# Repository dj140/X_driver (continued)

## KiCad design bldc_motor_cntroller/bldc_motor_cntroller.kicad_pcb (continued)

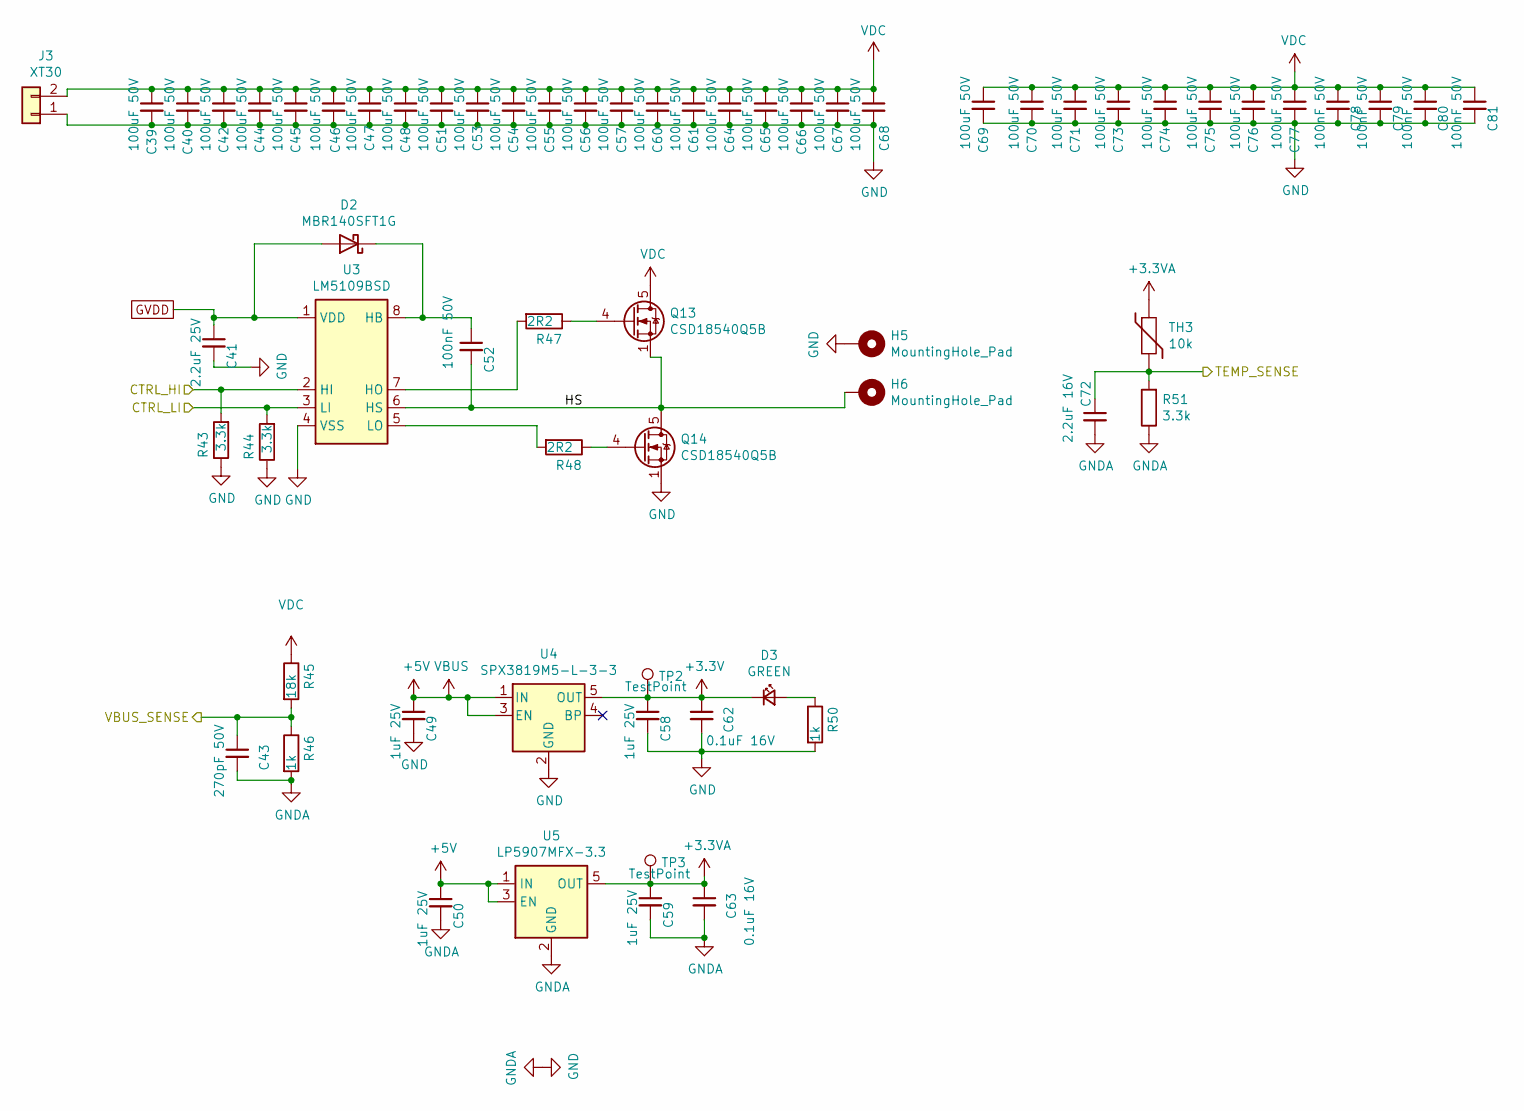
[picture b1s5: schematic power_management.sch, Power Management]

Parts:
C39, C40, C42, C44, C45, C46, C47, C48, C51, C53, C54, C55, C56, C57, C60, C61, C64, C65, C66, C67, C68, C69, C70, C71, C73, C74, C75, C76, C77: 100uF 50V; C_1206_3216Metric; MPN GMK105CC6105MV-F
C41: 2.2uF 25V; C_0402_1005Metric; MPN GMK105CC6105MV-F; LCSC Part # C12530
C43: 270pF 50V; C_0402_1005Metric; MPN GRM1555C1H271FA01D
C49, C50, C58, C59: 1uF 25V; C_0402_1005Metric; MPN GMK105CC6105MV-F; LCSC Part # C52923
C52: 100nF 50V; C_0402_1005Metric; MPN GMK105CC6105MV-F; LCSC Part # C1525
C62, C63: 0.1uF 16V; C_0402_1005Metric; MPN GRM155R62A104KE14D
C72: 2.2uF 16V; C_0402_1005Metric; MPN GRM155C81E225KE11D; LCSC Part # C12530
C78, C79, C80, C81: 100nF 50V; C_0402_1005Metric; MPN GMK105CC6105MV-F
D2: MBR140SFT1G; D_SOD-123F
D3: GREEN; LED_0402_1005Metric
H5, H6: MountingHole_Pad; TestPoint_Round
J3: XT30; AMASS_XT30PW-M_1x02_P2.50mm_Horizontal; MPN XT60
Q13, Q14: CSD18540Q5B; TDSON-8-1
R43, R44: 3.3k; R_0402_1005Metric; MPN CRCW040210K0FKEDC; LCSC Part # C25890
R45: 18k; R_0402_1005Metric; MPN CRCW040210K0FKEDC; LCSC Part # C25762
R46, R50: 1k; R_0402_1005Metric; MPN ERJ-2RKF1001X; LCSC Part # C11702
R47, R48: 2R2; R_0402_1005Metric; MPN CRCW040210K0FKEDC
R51: 3.3k; R_0402_1005Metric; MPN CRCW04023K30FKEDC; LCSC Part # C25890
TH3: 10k; R_0402_1005Metric; MPN CRCW040210K0FKEDC
TP2, TP3: TestPoint; TestPoint_Pad_D1.0mm
U3: LM5109BSD; WSON-8_4x4mm_P0.8mm
U4: SPX3819M5-L-3-3; SOT-23-5
U5: LP5907MFX-3.3; SOT-23-5

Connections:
+3.3VA: C59.1, C63.1, TH3.1, TP3.1, U5.5 (OUT); also elsewhere on the board
+3V3: C58.1, C62.1, D3.1 (K), TP2.1, U4.5 (OUT); also elsewhere on the board
+5V: C49.1, C50.1, U4.1 (IN), U4.3 (EN), U5.1 (IN), U5.3 (EN); also elsewhere on the board
/Microcontroller Interface/AUX_H: R43.2, U3.2 (HI); also elsewhere on the board
/Microcontroller Interface/AUX_L: R44.2, U3.3 (LI); also elsewhere on the board
/Microcontroller Interface/AUX_TEMP: C72.1, R51.2, TH3.2; also elsewhere on the board
/Microcontroller Interface/VBUS_S: C43.1, R45.2, R46.1; also elsewhere on the board
/Power Management/HS: C52.2, H6.1, Q13.1 (S), Q13.2 (S), Q13.3 (S), Q14.5 (D), U3.6 (HS)
GND: C39.2, C40.2, C41.2, C42.2, C43.2, C44.2, C45.2, C46.2, C47.2, C48.2, C49.2, C50.2, C51.2, C53.2, C54.2, C55.2, C56.2, C57.2, C58.2, C59.2, C60.2, C61.2, C62.2, C63.2, C64.2, C65.2, C66.2, C67.2, C68.2, C69.2, C70.2, C71.2, C72.2, C73.2, C74.2, C75.2, C76.2, C77.2, C78.2, C79.2, C80.2, C81.2, H5.1, J3.1, Q14.1 (S), Q14.2 (S), Q14.3 (S), R43.1, R44.1, R46.2, R50.2, R51.1, U3.4 (VSS), U3.9 (VSS), U4.2 (GND), U5.2 (GND); also elsewhere on the board
GVDD: C41.1, D2.2 (A), U3.1 (VDD); also elsewhere on the board
unnamed: C52.1, D2.1 (K), U3.8 (HB)
unnamed: D3.2 (A), R50.1
unnamed: Q13.4 (G), R47.1
unnamed: Q14.4 (G), R48.1
unnamed: R47.2, U3.7 (HO)
unnamed: R48.2, U3.5 (LO)
VDC: C39.1, C40.1, C42.1, C44.1, C45.1, C46.1, C47.1, C48.1, C51.1, C53.1, C54.1, C55.1, C56.1, C57.1, C60.1, C61.1, C64.1, C65.1, C66.1, C67.1, C68.1, C69.1, C70.1, C71.1, C73.1, C74.1, C75.1, C76.1, C77.1, C78.1, C79.1, C80.1, C81.1, J3.2, Q13.5 (D), R45.1; also elsewhere on the board

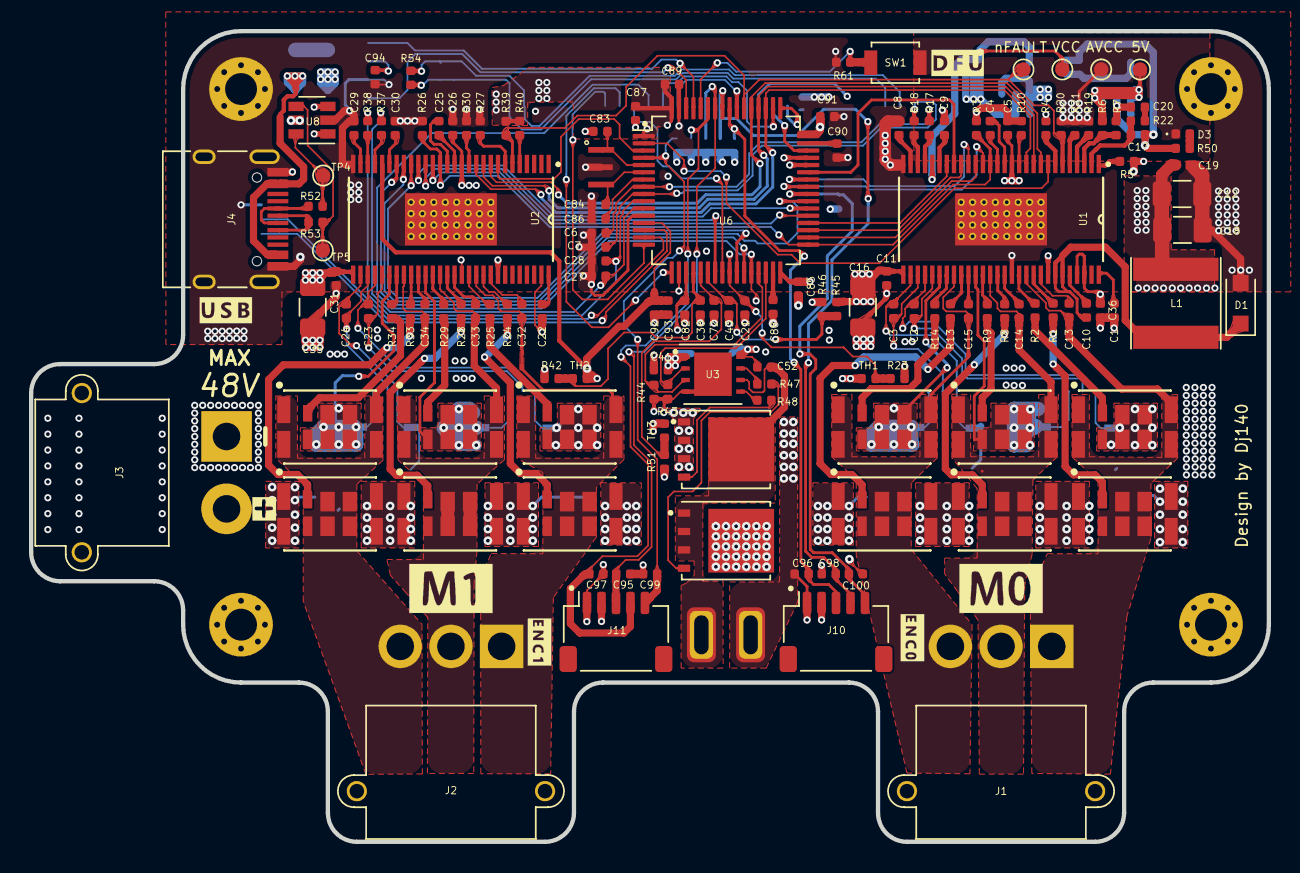
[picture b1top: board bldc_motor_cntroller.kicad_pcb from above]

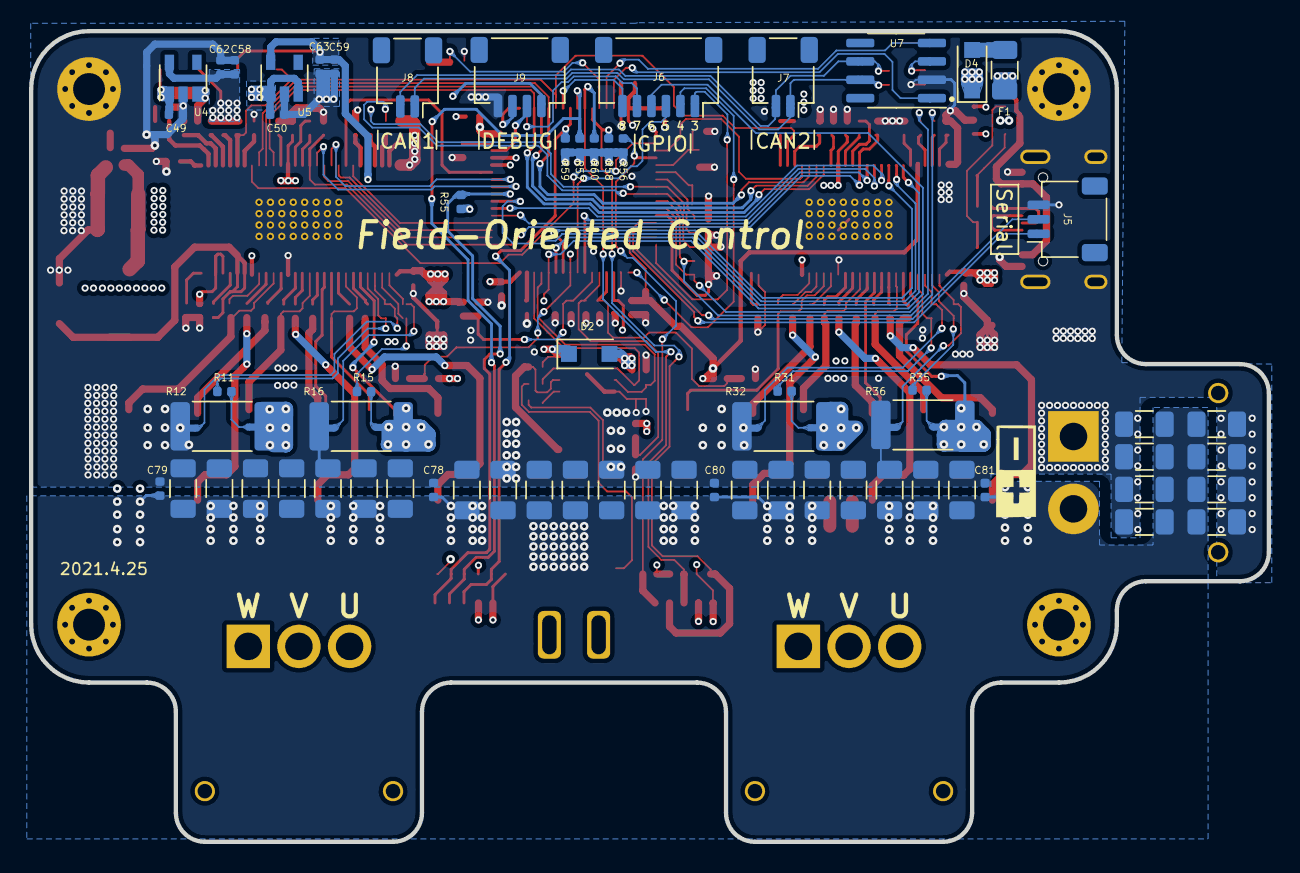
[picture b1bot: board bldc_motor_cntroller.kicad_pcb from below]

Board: 4 copper layers, 85.5 x 56.0 mm, 222 parts (72 on the bottom side), 155 nets.

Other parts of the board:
H1, H2, H3, H4: MountingHole_Pad; MountingHole_2.2mm_M2_Pad_Via

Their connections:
GND: H1.1, H2.1, H3.1, H4.1; also elsewhere on the board

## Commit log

2021-05-30 Add files via upload
    first commit
